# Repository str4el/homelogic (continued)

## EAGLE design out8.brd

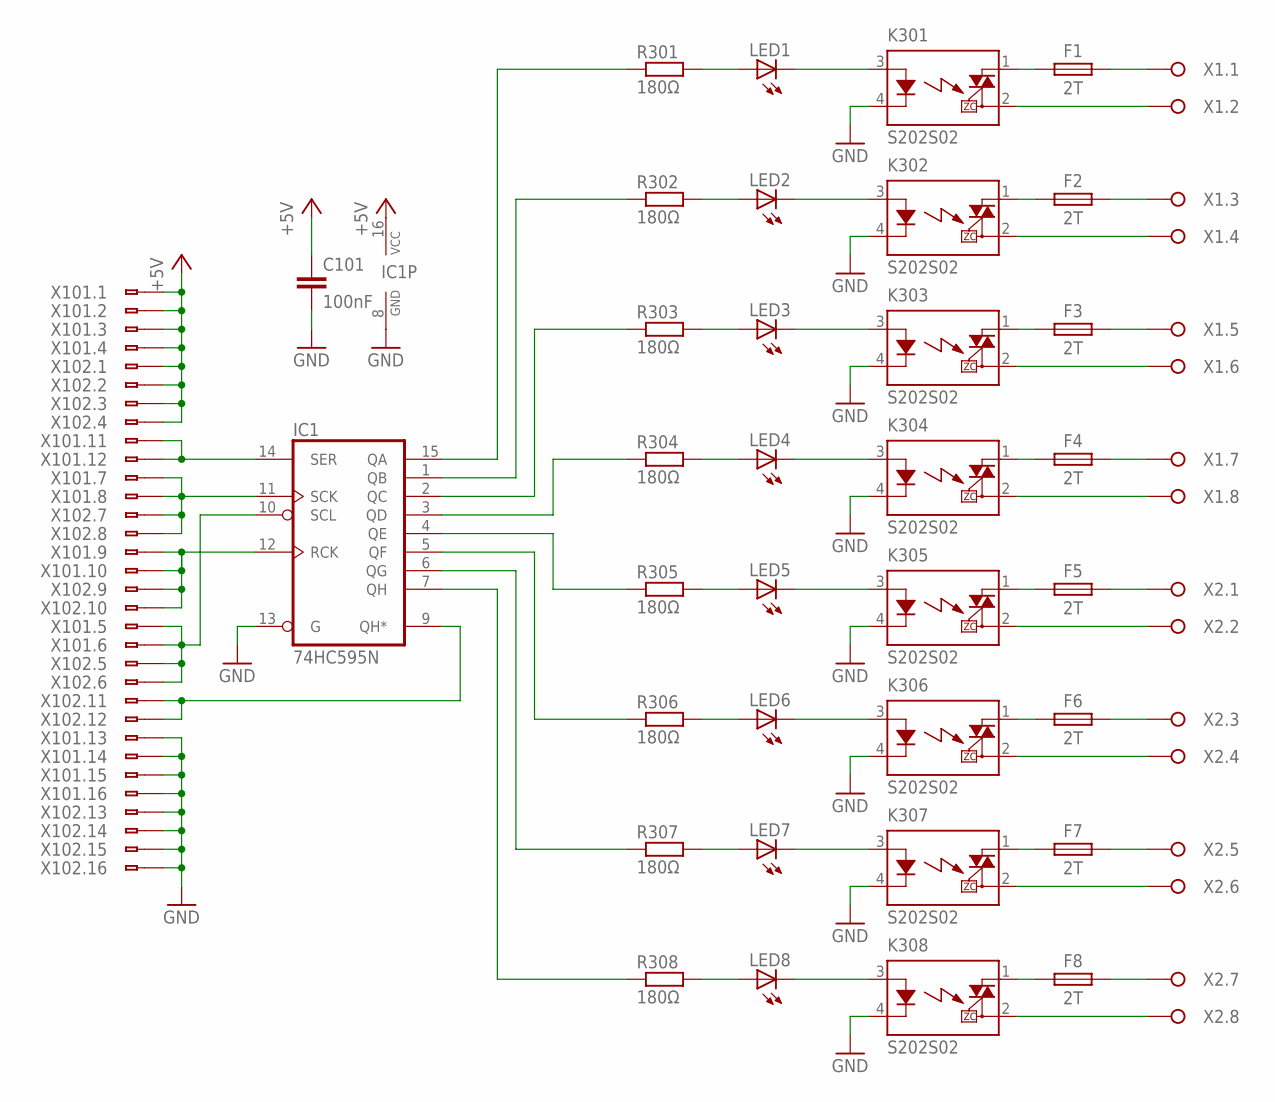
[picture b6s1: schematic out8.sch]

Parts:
C101: 100nF; C025-025X050
F1, F2, F3, F4, F5, F6, F7, F8: 2T; TR5
IC1: 74HC595N; DIL16
K301, K302, K303, K304, K305, K306, K307, K308: S202S02; SIP4
LED1, LED2, LED3, LED4, LED5, LED6, LED7, LED8: LED3MM
R301, R302, R303, R304, R305, R306, R307, R308: 180Ω; 0204/7
X1, X2: WAGO_236-408
X101, X102: WS16V

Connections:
!R: IC1.10 (SCL), X101.5, X101.6, X102.5, X102.6
+5V: C101.1, IC1.16 (VCC), X101.1, X101.2, X101.3, X101.4, X102.1, X102.2, X102.3, X102.4
C1: IC1.11 (SCK), X101.7, X101.8, X102.7, X102.8
C2: IC1.12 (RCK), X101.9, X101.10, X102.9, X102.10
D: IC1.14 (SER), X101.11, X101.12
GND: C101.2, IC1.8 (GND), IC1.13 (G), K301.4 (K), K302.4 (K), K303.4 (K), K304.4 (K), K305.4 (K), K306.4 (K), K307.4 (K), K308.4 (K), X101.13, X101.14, X101.15, X101.16, X102.13, X102.14, X102.15, X102.16
unnamed: IC1.15 (QA), R301.1
unnamed: IC1.1 (QB), R302.1
unnamed: IC1.2 (QC), R303.1
unnamed: IC1.3 (QD), R304.1
unnamed: IC1.4 (QE), R305.1
unnamed: IC1.5 (QF), R306.1
unnamed: IC1.6 (QG), R307.1
unnamed: IC1.7 (QH), R308.1
unnamed: F1.1, K301.1 (DS1)
unnamed: F1.2, X1.A1, X1.B1
unnamed: K301.2 (DS2), X1.A2, X1.B2
unnamed: F2.1, K302.1 (DS1)
unnamed: F2.2, X1.A3, X1.B3
unnamed: K302.2 (DS2), X1.A4, X1.B4
unnamed: F3.1, K303.1 (DS1)
unnamed: F3.2, X1.A5, X1.B5
unnamed: K301.3 (A), LED1.K (C)
unnamed: K302.3 (A), LED2.K (C)
unnamed: K303.3 (A), LED3.K (C)
unnamed: K304.3 (A), LED4.K (C)
unnamed: K305.3 (A), LED5.K (C)
unnamed: K306.3 (A), LED6.K (C)
unnamed: K307.3 (A), LED7.K (C)
unnamed: K308.3 (A), LED8.K (C)
unnamed: K303.2 (DS2), X1.A6, X1.B6
unnamed: F4.1, K304.1 (DS1)
unnamed: F4.2, X1.A7, X1.B7
unnamed: K304.2 (DS2), X1.A8, X1.B8
unnamed: F5.1, K305.1 (DS1)
unnamed: F5.2, X2.A1, X2.B1
unnamed: K305.2 (DS2), X2.A2, X2.B2
unnamed: F6.1, K306.1 (DS1)
unnamed: F6.2, X2.A3, X2.B3
unnamed: K306.2 (DS2), X2.A4, X2.B4
unnamed: F7.1, K307.1 (DS1)
unnamed: F7.2, X2.A5, X2.B5
unnamed: K307.2 (DS2), X2.A6, X2.B6
unnamed: F8.1, K308.1 (DS1)
unnamed: F8.2, X2.A7, X2.B7
unnamed: K308.2 (DS2), X2.A8, X2.B8
unnamed: IC1.9 (QH*), X102.11, X102.12
unnamed: LED1.A, R301.2
unnamed: LED2.A, R302.2
unnamed: LED3.A, R303.2
unnamed: LED4.A, R304.2
unnamed: LED5.A, R305.2
unnamed: LED6.A, R306.2
unnamed: LED7.A, R307.2
unnamed: LED8.A, R308.2

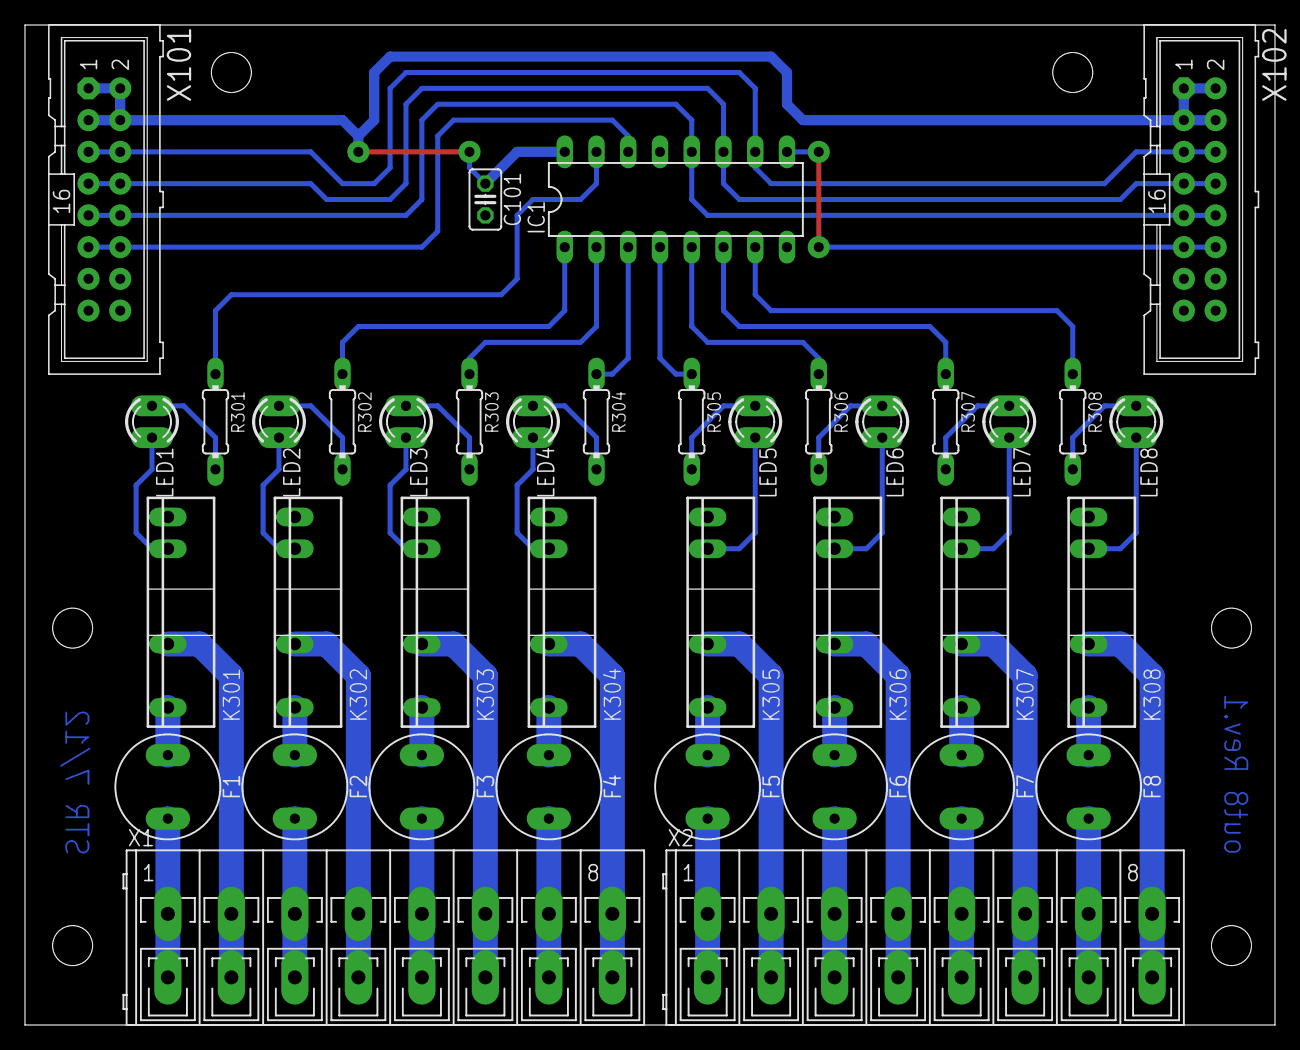
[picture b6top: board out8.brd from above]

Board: 2 copper layers, 100.0 x 80.0 mm, 38 parts (0 on the bottom side), 55 nets.

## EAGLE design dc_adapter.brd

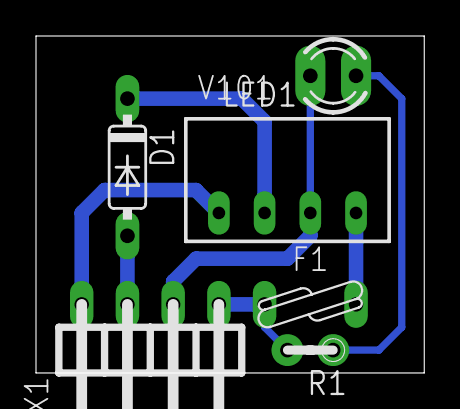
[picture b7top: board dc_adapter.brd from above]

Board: 2 copper layers, 21.6 x 18.7 mm, 6 parts (0 on the bottom side), 7 nets.

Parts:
D1: DO35-7
F1: LP60-020
LED1: LED3MM
R1: 390Ω; 0204V
V101: TME2405S; TME-24V
X1: STG4

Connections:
unnamed: V101.1, X1.1
unnamed: D1.C, V101.2
unnamed: D1.A, X1.2
unnamed: F1.P$2, V101.4
unnamed: LED1.K, V101.3, X1.3
unnamed: LED1.A, R1.1
unnamed: F1.P$1, R1.2, X1.4

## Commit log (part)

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2012-07-15 Schematic und Layout erstellt
2012-07-15 74594 durch 74HC594 ersetzt
2012-07-15 Leichte korrekturen an Schematik und Layout
2012-07-17 Echtzeituhr eingebaut
2012-07-17 Werte korrigiert
2012-07-19 Achtfach-Ausgangsmodul erstellt
2012-07-22 Multimaster mit 16 Eingängen erstellt
2012-07-22 Busstecker auf Ausgangsboard ersetzt; kleinere Layoutanpassungen
2012-07-22 Batterie auf Multimaster hinzugefügt
2012-07-24 Dipschalter durch Drehschalter ersetzt; 74HC594 durch 74HC595 ersetzt; Signalleitungen gedreht.
2012-07-26 Leiterbahn verschoben
2012-07-26 Alarme angeschlossen; Detailverbesserungen am Layout
2012-07-26 Werte im Schema und Bohrungen im Layout hinzugefügt
2012-07-28 Anschlussklemmen ausgetauscht
2012-07-28 Optionaler Abschlusswiderstand eingefügt
2012-07-28 Batteriehalter ausgetauscht
2012-07-28 Erstes Testprogamm geschrieben
2012-07-29 Eingangsverarbeitung modifiziert
2012-07-29 BUGFIX: i2c Slaveadressierung falsch
2012-07-29 i2c_pread/i2c_pwrite hinzugefügt
2012-07-29 rct.h erstellt
2012-07-31 BUGFIX: Eingänge werden nicht gelesen; Ausgänge nicht geschrieben.
2012-08-02 Bus implementierung begonnen
2012-08-04 Busprotokoll angepasst
2012-08-05 Busdecodierung für Bitchange implementiert
2012-08-05 rtc_time2str implementiert; BUGFIX: bcs wird nicht gesendet und eb1 wird nicht eingelesen
2012-08-05 BUGFIX: Nur jede zweite Nachricht wurde empfangen
2012-08-07 Fehler in der i2c implementierung beseitigt; Stellen der Uhr implementiert
2012-08-09 Programmbearbeitung implementiert; Vorangigkeit funktioniert noch nicht
2012-08-09 BUGFIX: SDT funktioniert nicht mit jeder Zeit
2012-08-13 Mergeleiche entfernt; Defaultlayer aktiviert
2012-09-03 Zwei fehlende break in prog_cycle() ergänzt
2012-09-04 Progammablauf an neuen Code angepasst; RUN, STP und PRG implementiert
2012-09-05 BUGFIX: UN, ON und = funktionieren nicht richtig
2012-09-11 dc_adapter erstellt
2012-09-12 Debugfunktion implementiert
2012-09-12 Debugfunktion erweitert; BUGFIX: Progarammablauf fehlerhaft bei S, R und X
2012-09-18 Sicherheit und LED für Spannungsversorgung hinzugefuegt
2012-11-27 BUGFIX: Bei Serienschaltern reagieren manchmal beide Eingänge
    Das Problem kommt vermutlich von einer kapazitiven überlagerung auf der
    Schaltleitung. Das Eingangssignal muss jetzt länger anstehen bevor
    darauf reagiert wird. Das löst hoffentlich das Problem.
2012-11-27 Identifizierung hinzugefügt
2013-04-22 Homelogic unter die GPLv3 gestellt
2013-04-22 Bauteile neu positoniert
2013-04-22 Erste vorläufige Implementation
2013-04-22 kleinere Designfehler beseitigt
2013-04-22 Fehlende Leiterbahn erzeugt; keine Stopmaske bei Vias
2013-04-22 Beschriftung angepasst
2013-04-22 Halbleiterrelais wegen gehäuse versetzt
2013-04-22 Leiterbahnführung verbessert; Analog ground verbessert
2013-04-22 Batteriespannungsdioden versetzt
2013-04-22 Schematik übersichtlicher gemacht; Bauteile neu benannt; Werte ergänzt
2013-04-22 Netzklasse netz erstellt und zugeordnet
2013-04-22 Bauteile wegen Beschriftung ausgetauscht
2013-04-22 Bezeichnungen angepasst; Position auf Board angepasst
2013-04-22 Eingänge auf ltv-354t umgestellt
2013-05-06 Wert von D101 geändert
2013-05-06 Anschlüsse versetzt
    Anschlüsse sind jetzt nicht mehr korrekt unter den Löchern dafür
    müsste die Platine aber ins Gehäuse passen
2013-07-05 Firmware an neue Hardware angepasst; Hardwarewahl per Define
2013-07-05 Warnungen durch casts reduziert
2013-07-05 Bus Empfangsroutienen überarbeitet
2013-07-09 Depends aus Makefile entfernt
2013-07-09 Speicherinformationen implememtiert
2013-08-13 bus_send_message_* funktionen erstellt; busfunktionen teilweise umbenannt.
2013-08-13 bus_send_data_* entfernt und durch bus_send_message_* ersetzt
2013-08-14 Busbefehl SET hinzugefügt
2013-08-15 deps jetzt außerhalb des Makefiles; git describe für Version verwendet
2013-08-18 Grundstein des Compilers gelegt
2013-08-19 hlc_compile implementiert
2013-08-20 hlc_write_hexfile erstellt
2013-08-21 Programmlänge aus sicht des compilers variabel gemacht
2013-08-21 hll_ladefuktionen implementiert
2013-09-19 hlterm jetzt direkt über ftdi möglich
2013-09-24 Probleme mit Makefile behoben
2013-09-24 BUGFIX: Reagiert nicht auf Busbefehle
2013-09-24 LED funktionalität erweitert
2013-09-25 Statusänderung nur am Anfang des Zyklus möglich
2013-09-26 CRC für Programm implementiert
2013-10-01 Konzept überarbeitet; Synchronisierung der Bibliothek mit der Firmware:
    - C-Bibliothek für Programmierung und Komunikation
    - Ablaufprogramm nun mit Header und CRC Prüfung
    - Dynamische speicherverwaltung der Firmware
    - Datenübertragung jetzt Wortweise
    - Bibliothek und Firmware benutzen die selbe Basis
    Der Interpreter ist bis jetzt nur gerinfügig zum Testen implementiert.
2013-10-02 Testprogramme hinzugefügt
2013-10-02 Dateien umbenannt
2013-10-03 Makefiles überarbeitet und die konfiguration der firmware vereinfacht
2013-10-03 Funktions- und Variablennamen umbenannt für weitere Zusammenführung der Bibliothek
2013-10-03 Datenstrukturen hlc_t und hlload_t zusammengeführt
2013-10-03 BUGFIX: Datenfehler nach stop und run
2014-01-09 Terminal auf Stream geändert
2014-01-09 Testprogramme auf Streamterminal geändert
2014-01-09 Bustimings verlängert
2014-01-22 Businit setzt Buslock
2014-01-22 virtualbus implementiert
2014-01-22 Terminal und Testprogramme auf vbus umgestellt
2014-01-22 terminal in connector umbenannt
2014-01-23 Verwendete Eingänge werden der address_map der verantwortlichen CPU hinzugefügt
2014-01-23 Eigene eeprom implementierung entfernt und durch libavr ersetzt
2014-01-27 BUGFIX: Unbekannter Befehl bei zu vielen Interrupts
2014-01-27 bool.h durch stdbool ersetzt; lib C++ tauglich gemacht
2014-01-27 BUGFIX: Bits der ungeraden Bytes werden nicht verarbeitet
2014-01-29 Klammerverarbeitung implementiert
2014-01-29 Programmablauf vereifacht durch funktionszusammenführung
2014-01-30 XOR implementiert
2014-01-30 Laden von Konstanten implementiert
2014-01-30 Wortverarbeitung von and, or und xor implementiert
2014-01-31 BUGFIX: Programmende nur bei einer CPU
2014-01-31 Errorstrings erstellt
2014-02-01 CPUs werden jetzt sequenziel geladen
2014-02-01 Testprogamme hlc hlload hlterm entfernt; Bibliothek aufgeräumt
2014-02-05 BUGFIX: Shared library wird nicht richtig erstellt
2014-02-12 Timer implementiert
2014-02-12 Workaround: virtualbus blockiert beim senden
2014-02-12 Stellen und anzeigen der Echtzeituhr wieder implementiert
2014-02-18 Zähler, Vergleicher und Rechenoperationen implementiert
2014-02-21 Toolchain für verschiedene MCUs vorbereitet
2014-02-22 Einfache Moudle für fhem geschrieben
2014-02-23 BUGFIX: strenoperator bei sizeof in compiler_init vergessen
2014-02-23 NoVerify option zu connector hinzugefügt.
    Damit sollten auch standard 485 Adapter funktionieren,
    habe es aber noch nicht getestet.
2014-02-23 Variablen in Makefile sollen erstellt werden, nicht gespeichert
2014-02-23 MCU_ define zu config.h hinzugefügt
2014-02-23 MCU spezifisches in entsprechenden header verlegt; at1284p hinzugefügt
2014-02-23 Copyright informationen aktualisiert
2014-02-23 MCU Anzeige bei IDY
2014-02-27 BUGFIX: Endlosreset auf atmega1284
2014-02-27 Getrenter Ausgang und Pulsfunktion zu Fhemmodul hinzugefügt
2014-02-28 Datenübertragung der Zähler implementiert
2014-02-28 Busbefehl dump auf Zeiten und Zähler erweitert
2014-02-28 Systemzeit über Eingänge abfragbar
2014-03-08 BUGFIX: Beim Prototype wird noch die Adresse verdoppelt
2014-03-08 BUGFIX: Keine Hysterese bei Temperatur- und Batteriewarnung; Temperaturwerteabschaltwerte angepasst.
2014-07-28 Verbindungszähler in virtualbus implementiert
2014-09-21 Foobar in GPL Header durch Homelogic ersetzt
2014-09-28 Revision 2 von dig_ac230 wird zur USB variante
2014-09-28 dig_usb auf AT90USB1287 umgestellt
2014-10-05 Einiges auf dig_usb controllerboard gerouted
2014-10-08 USB Stecker und Quarz hinzugefügt
2014-10-08 dig_usb vorläufig komplett geroutet
2014-10-09 Padgröße bei Wannenstecker für dig_usb angepasst
2014-10-09 Widerstandsarrays für LEDs gegen CHIP0805 bei dig_usb getauscht
2014-10-11 Unterer Wannenstecker auf dig_usb verschoben um Platz für Wärmebrücke zu machen
2014-10-20 USB Buchse ausgetauscht
2014-10-22 UVCC und HWB angeschlossen
2014-10-22 Steckbare Anschlüsse zu dig_usb hinzugefügt
2014-10-22 RJ45 Buchsen für Bus an dig_usb
2014-10-23 Routing auf dig_usb verfeinert
2014-10-26 dig_usb: Beschriftung besser angeordnet
2014-10-26 dig_usb: Platinen zusammengeführt
2014-11-10 Alternativer DC/DC Wandler und Ausgangsfilter hinzugefügt
2014-11-11 Testpads hinzugefügt
2014-11-17 Zusätzlicher Kondensator für UVcc; HWB mit INT4 verbunden
2014-12-13 Minimale abstandskorrektur
2014-12-13 Grundgerüst für neues menu geschaffen
2014-12-13 Firmware an neues Buildsystem angepasst
2014-12-13 templatefile entfernt; deps wieder scharf gemacht
2014-12-13 Auskommentiertes include entfernt
2014-12-16 prog_status werte umbenannt um Konflickt mit DEBUG Flag zu beseitigen
2014-12-16 Baudrate kann jetzt über menuconfig eingestellt werden
2014-12-16 MCU auswahl jetzt über bedingte Quelle
2014-12-27 hardware.h der firmware wird jetzt durch m4 makros erstellt
2014-12-27 Überflüssige header gelöscht
2014-12-27 Lesen der Eingänge vereinheitlicht
2014-12-29 I2C Bustiming wird jetzt im menu eingestellt
2014-12-29 Pin Initialisierung und Hardwaremonitor abstrahiert
2014-12-29 RTC und I2C jetzt optional; usb_cpu hinzugefügt
2014-12-30 BUGFIX: DDR für rote LED auf CPU USB falsch
2014-12-30 Ausgangsabschaltung bei Übertemperatur gefixt
2015-01-03 Timerinitialisierung vereinheitlicht
2015-01-03 BUGFIX: Bus funktioniert nicht mehr seit commit c9b18e6
2015-01-03 Kleinichkeiten gefixt
2015-01-03 program und fuses in Buildsystem eingeführt
2015-01-04 ADC Prescaler abstarhiert; MCU-spezifische C Dateien entfernt
2015-01-04 Neues SFR system für read_adc übernommen
2015-01-04 submodule lufa hinzugefügt
2015-01-06 USB_CPU zu CPU_USB umbenannt
2015-01-06 Virtuelle serielle Schnittstelle implementiert
2015-02-06 Tippfehler int defaults.mk bereinigt
2015-05-27 Eigenen USB Descriptor erstellt
2015-06-30 usb.mk vergessen
2015-07-21 Logo und Beschriftung erstellt
2015-07-21 Schriftart für Deckelbeschriftung geändert
2015-07-22 BUGFIX: Doppelinitialisierung des Programms bei wechsel von RUN auf DEBUG
2015-07-22 Nebenläufige aktionen in yield() verschoben
    Wichtige nebenläufige Funktionen werden nun in der Funktion
    yield() aufgerufen. Diese muss dann von der Hautschleife und
    alle anderen Warteschleifen aufgerufen werden.
2015-07-23 Programmanalysierer geschrieben
2015-07-23 usb_send_data asynchron gestaltet
2015-07-23 Deklaration von usb_configuration_t von usb.h nach usb.c verschoben
2015-07-23 Hysterese der Temperaturwarnung angepasst
2015-07-23 BUGFIX: Daten über USB werden zurückgesendet
2015-07-24 pana: Einrückung hinzugefügt
2015-09-14 Kontextsensetiver Tokenizer für lexikalische Analyse erstellt
2015-09-21 Scannen von Symbolen auf den neuen tokenizer umgestellt
2015-09-24 Weitere Funktionen an den neuen Tokenizer angepasst
2015-09-25 Ein paar Funktionen in compiler.c Kommentiert
2015-09-29 BUGFIX: Reihenfolge der Ein- und Ausgänge bei CPU_USB vertauscht
2015-12-22 BUGFIX: Bitreihenfolge der IOs bei USB_CPU vertauscht
2015-12-24 USB Puffer vergrößert um fehlende Nachrichten zu verhindern
2015-12-24 Noverify zur Standarteinstellung bei hlm gemacht
2016-02-23 Türmodul innen hinzugefügt
2016-02-24 Detailverbesserungen an Türmodul
2016-08-17 Minimale Layoutverbesserung im Türmodul
2016-08-29 Präprozessor implementiert TODO: Fehlerrückmeldung für lib vereinheitlichen
2016-10-14 Kompiler überarbeitung
2016-10-14 BUGFIX: Ein Block zu wenig ausgegeben
2016-10-18 Compiler wider funktionsfähig
2016-10-18 Warnungen verhindert
2016-11-27 Äußeres Türmodul überarbeitet
2016-12-06 Türaußenmodul abgeschlossen
2016-12-06 Türmodul benannt
2016-12-06 Türmodule umbenannt
2017-01-17 Label und Target erkennung in Compiler implementiert
2017-01-18 BUGFIX: Homelogic startet ständig neu
2017-01-19 Laden in libhl und hlm überarbeitet
2017-01-19 BUGFIX: Loader lädt unnötige nullen am Programmende
2017-01-19 Auskomentierung zum Debug im Code vergessen
2017-01-19 Ausgabe von pana erweitert
2017-01-20 BUGFIX: BUGFIX hat Zeiten sofort ablaufen lassen
2017-01-20 BUGFIX: Nach BUGFIX BUGFIX werden counter nicht mehr geladen
2017-01-25 Doc zur erstellung der Firmware hinzugefügt
2017-01-25 Menuconfig wird nur noch von Firmware benutzt; Den rest von Build dateien gesäubert
2017-01-27 Verwende Autotools für lib und hlm
